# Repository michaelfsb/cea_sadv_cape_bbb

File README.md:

# cea_sadv_cape_bbb
Projeto no KiCad de um módulo para aquisição dados em voo realizado no projeto de Iniciação Cientifica intitulado "Modernização do Sistema de Aquisição de Dados de Voo do CEA".

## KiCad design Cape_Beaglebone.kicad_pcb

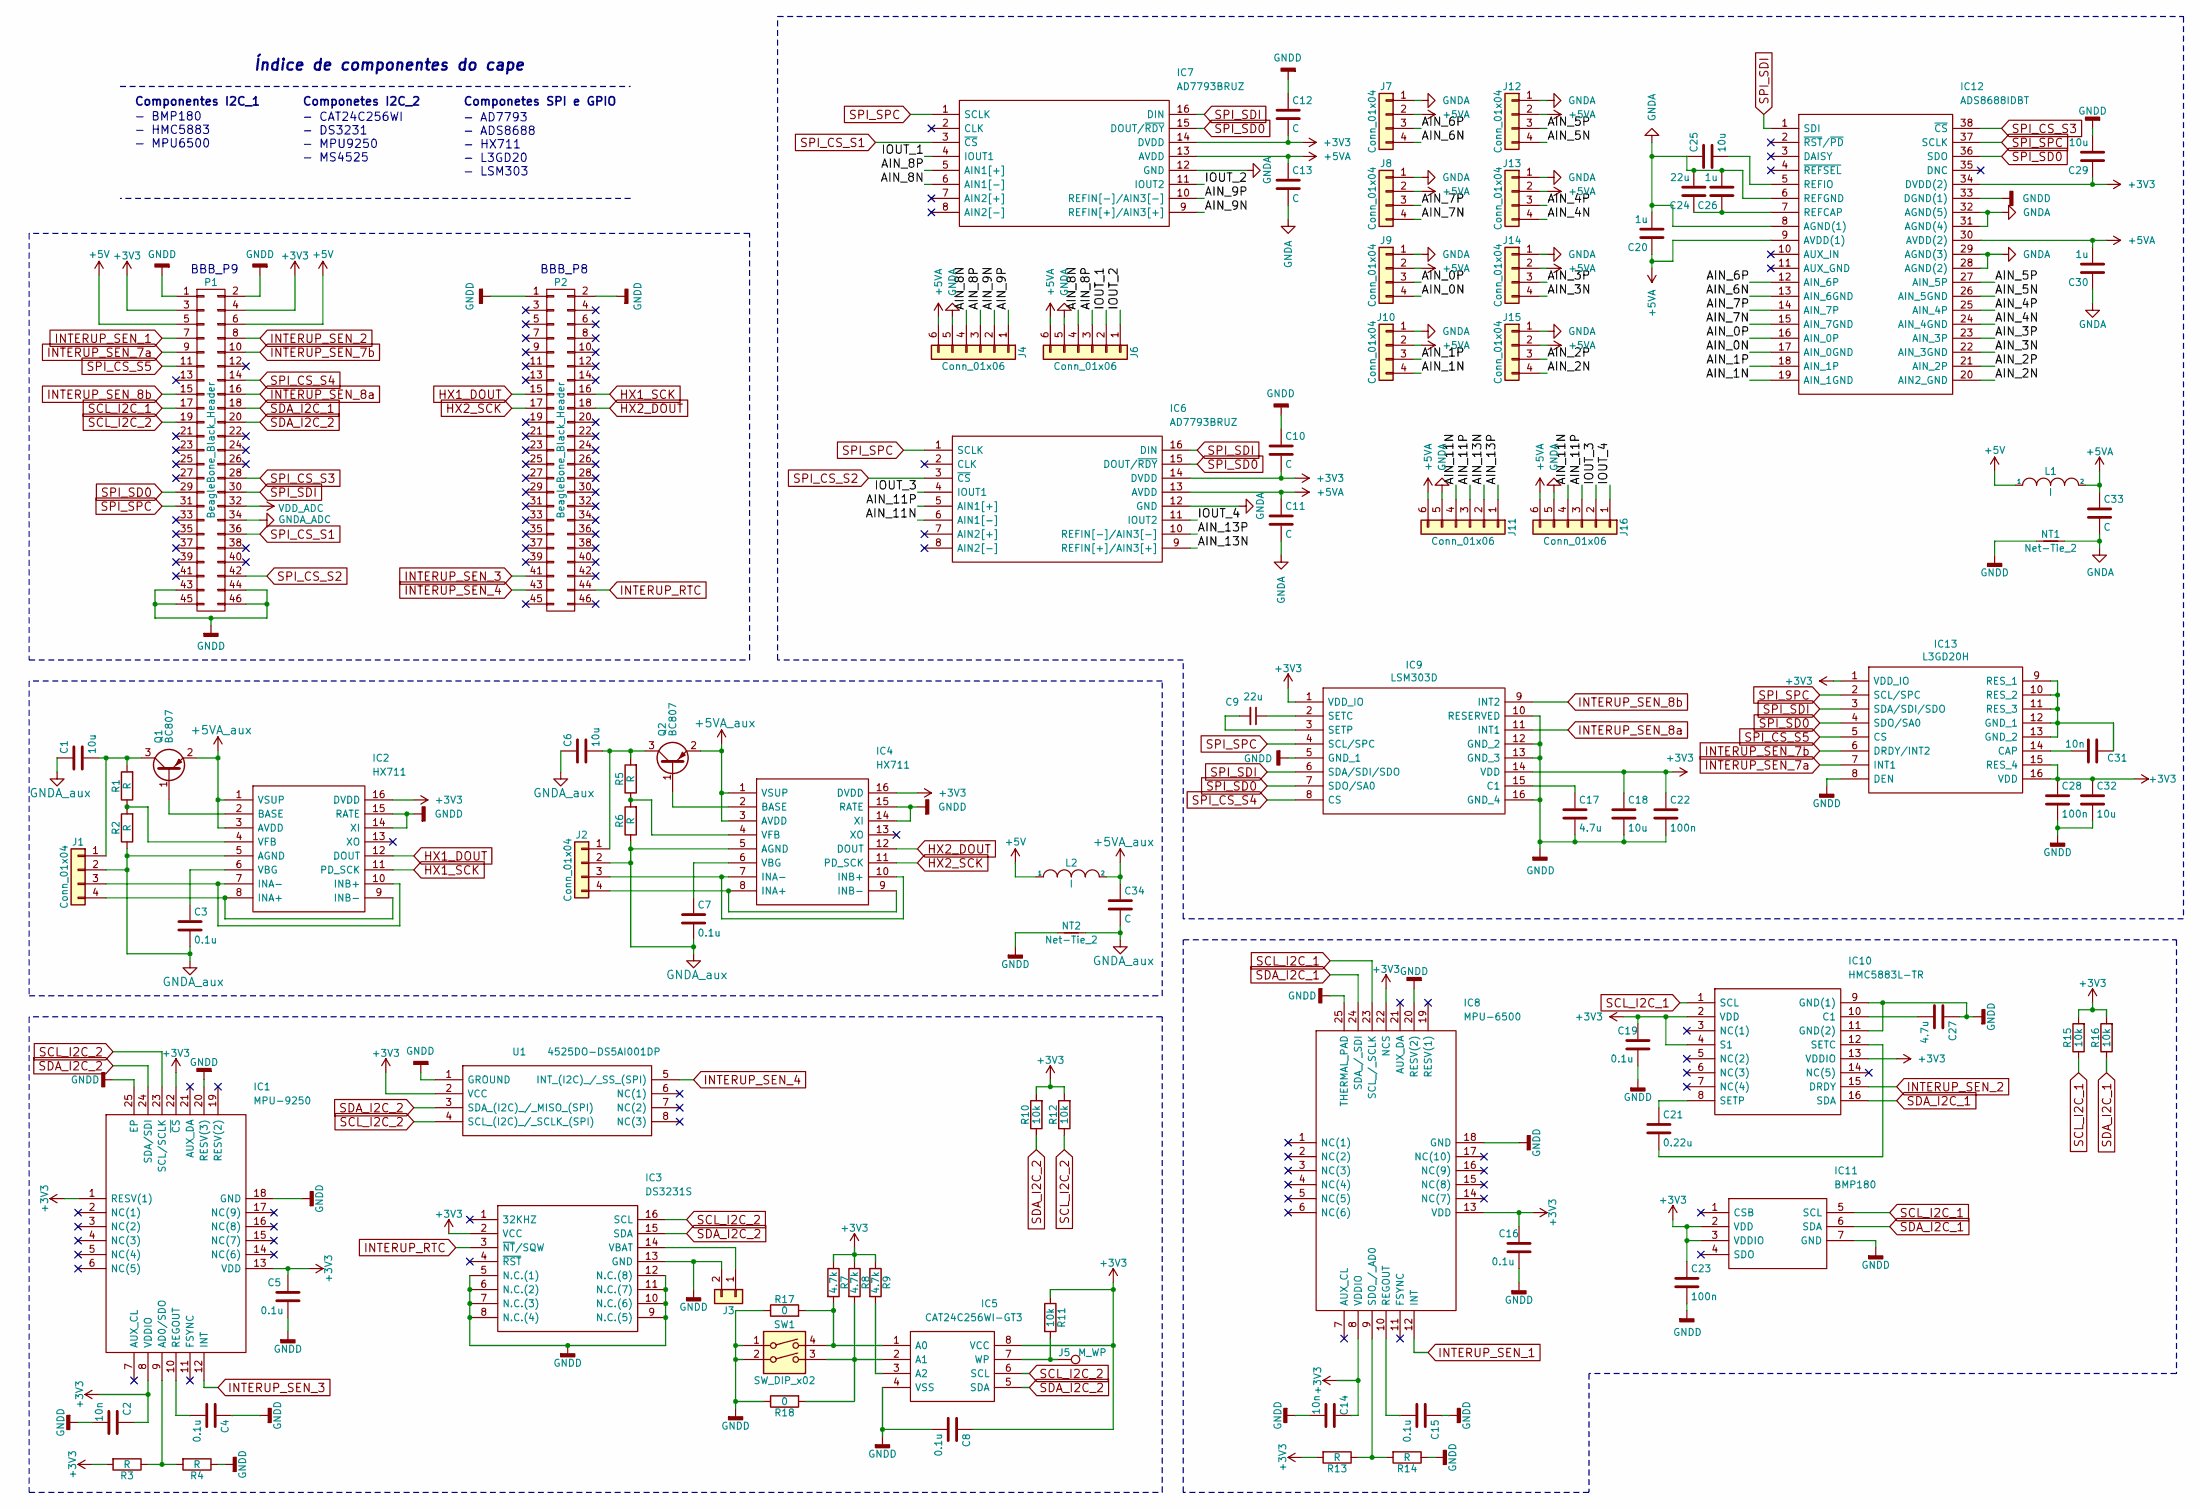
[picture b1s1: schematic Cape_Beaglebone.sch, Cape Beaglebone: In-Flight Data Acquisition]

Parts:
C1, C6, C18, C25, C29, C32: 10u; C_0805
C2, C14, C31: 10n; C_0805
C3, C4, C5, C7, C8, C15, C16, C19: 0.1u; C_0805
C9, C24: 22u; C_0805
C10, C11, C12, C13, C33, C34: C; C_0805
C17, C27: 4.7u; C_0805
C20, C26, C30: 1u; C_0805
C21: 0.22u; C_0805
C22, C23, C28: 100n; C_0805
IC1: MPU-9250; QFN40P300X300X105-25N-D; Manufacturer_Part_Number MPU-9250
IC2, IC4: HX711; SOIC127P600X160-16N; Manufacturer_Part_Number HX711
IC3: DS3231S; SOIC127P1032X265-16N; Manufacturer_Part_Number DS3231S#
IC5: CAT24C256WI-GT3; SOIC127P800X203-8N; Manufacturer_Part_Number CAT24C256WI-GT3
IC6, IC7: AD7793BRUZ; SOP65P640X120-16N; Manufacturer_Part_Number AD7793BRUZ
IC8: MPU-6500; QFN40P300X300X95-25N-D; Manufacturer_Part_Number MPU-6500
IC9: LSM303D; PQFN50P300X300X100-16N; Manufacturer_Part_Number LSM303D
IC10: HMC5883L-TR; 16-PIN-LPCC; Manufacturer_Part_Number HMC5883L-TR
IC11: BMP180; Manufacturer_Part_Number BMP180
IC12: ADS8688IDBT; SOP50P640X120-38N; Manufacturer_Part_Number ADS8688IDBT
IC13: L3GD20H; LGA(3X3X1.0-16L); Manufacturer_Part_Number L3GD20H
J1, J2, J7, J8, J9, J10, J12, J13, J14, J15: Conn_01x04; JST_SH_BM04B-SRSS-TB_04x1.00mm_Straight
J3: Conn_01x02; JST_SH_BM02B-SRSS-TB_02x1.00mm_Straight
J4, J6, J11, J16: Conn_01x06; JST_SH_BM06B-SRSS-TB_06x1.00mm_Straight
J5: M_WP; test_pad
L1, L2: I; R_Axial_DIN0204_L3.6mm_D1.6mm_P7.62mm_Horizontal
NT1, NT2: Net-Tie_2; net_tie2
P1, P2: BeagleBone_Black_Header; Socket_BeagleBone_Black
Q1, Q2: BC807; SOT-23
R1, R2, R3, R4, R5, R6, R13, R14: R; R_0603
R7, R8, R9: 4.7k; R_0603
R10, R11, R12, R15, R16: 10k; R_0603
R17, R18: 0; R_0603
SW1: SW_DIP_x02; SW_DIP_x2_W5.08mm_Slide_Copal_CHS-A
U1: 4525DO-DS5AI001DP; 4525DO-DS...P; Manufacturer_Part_Number 4525DO-DS5AI001DP

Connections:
+3V3: C2.1, C5.1, C8.1, C10.2, C12.2, C14.1, C16.1, C18.1, C19.1, C22.1, C23.1, C28.1, C29.1, C32.1, IC1.1 (RESV(1)), IC1.8 (VDDIO), IC1.13 (VDD), IC1.22 (~CS), IC2.16 (DVDD), IC3.2 (VCC), IC4.16 (DVDD), IC5.8 (VCC), IC6.14 (DVDD), IC7.14 (DVDD), IC8.8 (VDDIO), IC8.13 (VDD), IC8.22 (NCS), IC9.1 (VDD_IO), IC9.14 (VDD), IC10.2 (VDD), IC10.4 (S1), IC10.13 (VDDIO), IC11.2 (VDD), IC11.3 (VDDIO), IC12.34 (DVDD(2)), IC13.1 (VDD_IO), IC13.15 (RES_4), IC13.16 (VDD), P1.3, P1.4, R3.2, R7.1, R8.1, R9.1, R10.2, R11.1, R12.2, R13.2, R15.2, R16.2, U1.2 (VCC); also elsewhere on the board
+5V: L1.1, L2.1, P1.5, P1.6; also elsewhere on the board
+5VA: C11.1, C13.1, C20.1, C30.2, C33.1, IC6.13 (AVDD), IC7.13 (AVDD), IC12.9 (AVDD(1)), IC12.30 (AVDD(2)), J4.6, J6.6, J7.2, J8.2, J9.2, J10.2, J11.6, J12.2, J13.2, J14.2, J15.2, J16.6, L1.2
+5VA_aux: C34.1, IC2.1 (VSUP), IC2.3 (AVDD), IC4.1 (VSUP), IC4.3 (AVDD), L2.2, Q1.2 (E), Q2.2 (E)
/AIN_0N: IC12.17 (AIN_0GND), J9.4
/AIN_0P: IC12.16 (AIN_0P), J9.3
/AIN_1N: IC12.19 (AIN_1GND), J10.4
/AIN_1P: IC12.18 (AIN_1P), J10.3
/AIN_2N: IC12.20 (AIN2_GND), J15.4
/AIN_2P: IC12.21 (AIN_2P), J15.3
/AIN_3N: IC12.22 (AIN_3GND), J14.4
/AIN_3P: IC12.23 (AIN_3P), J14.3
/AIN_4N: IC12.24 (AIN_4GND), J13.4
/AIN_4P: IC12.25 (AIN_4P), J13.3
/AIN_5N: IC12.26 (AIN_5GND), J12.4
/AIN_5P: IC12.27 (AIN_5P), J12.3
/AIN_6N: IC12.13 (AIN_6GND), J7.4
/AIN_6P: IC12.12 (AIN_6P), J7.3
/AIN_7N: IC12.15 (AIN_7GND), J8.4
/AIN_7P: IC12.14 (AIN_7P), J8.3
/AIN_8N: IC7.6 (AIN1[-]), J4.4, J6.4
/AIN_8P: IC7.5 (AIN1[+]), J4.3, J6.3
/AIN_9N: IC7.9 (REFIN[+]/AIN3[+]), J4.2
/AIN_9P: IC7.10 (REFIN[-]/AIN3[-]), J4.1
/AIN_11N: IC6.6 (AIN1[-]), J11.4, J16.4
/AIN_11P: IC6.5 (AIN1[+]), J11.3, J16.3
/AIN_13N: IC6.9 (REFIN[+]/AIN3[+]), J11.2
/AIN_13P: IC6.10 (REFIN[-]/AIN3[-]), J11.1
/IOUT_1: IC7.4 (IOUT1), J6.2
/IOUT_2: IC7.11 (IOUT2), J6.1
/IOUT_3: IC6.4 (IOUT1), J16.2
/IOUT_4: IC6.11 (IOUT2), J16.1
GNDA: C11.2, C13.2, C20.2, C24.2, C25.1, C26.2, C30.1, C33.2, IC6.12 (GND), IC7.12 (GND), IC12.6 (REFGND), IC12.8 (AGND(1)), IC12.28 (AGND(2)), IC12.29 (AGND(3)), IC12.31 (AGND(4)), IC12.32 (AGND(5)), J4.5, J6.5, J7.1, J8.1, J9.1, J10.1, J11.5, J12.1, J13.1, J14.1, J15.1, J16.5, NT1.2
GNDA_aux: C1.1, C3.2, C6.1, C7.2, C34.2, IC2.5 (AGND), IC4.5 (AGND), J1.2, J2.2, NT2.2, R2.1, R6.1
GNDD: C2.2, C4.1, C5.2, C8.2, C10.1, C12.1, C14.2, C15.1, C16.2, C17.2, C18.2, C19.2, C22.2, C23.2, C27.1, C28.2, C29.2, C32.2, IC1.18 (GND), IC1.20 (RESV(3)), IC1.25 (EP), IC2.14 (XI), IC2.15 (RATE), IC3.5 (N.C.(1)), IC3.6 (N.C.(2)), IC3.7 (N.C.(3)), IC3.8 (N.C.(4)), IC3.9 (N.C.(5)), IC3.10 (N.C.(6)), IC3.11 (N.C.(7)), IC3.12 (N.C.(8)), IC3.13 (GND), IC4.14 (XI), IC4.15 (RATE), IC5.4 (VSS), IC8.18 (GND), IC8.20 (RESV(2)), IC8.25 (THERMAL_PAD), IC9.5 (GND_1), IC9.10 (RESERVED), IC9.12 (GND_2), IC9.13 (GND_3), IC9.16 (GND_4), IC10.9 (GND(1)), IC10.11 (GND(2)), IC11.7 (GND), IC12.33 (DGND(1)), IC13.8 (DEN), J3.2, NT1.1, NT2.1, P1.1, P1.2, P1.43, P1.44, P1.45, P1.46, P2.1, P2.2, R4.1, R14.1, R17.1, R18.1, SW1.1, SW1.2, U1.1 (GROUND); also elsewhere on the board
HX1_DOUT: IC2.12 (DOUT), P2.15; also elsewhere on the board
HX1_SCK: IC2.11 (PD_SCK), P2.16; also elsewhere on the board
HX2_DOUT: IC4.12 (DOUT), P2.18; also elsewhere on the board
HX2_SCK: IC4.11 (PD_SCK), P2.17; also elsewhere on the board
INTERUP_RTC: IC3.3 (~NT~/SQW), P2.44; also elsewhere on the board
INTERUP_SEN_1: IC8.12 (INT), P1.7; also elsewhere on the board
INTERUP_SEN_2: IC10.15 (DRDY), P1.8; also elsewhere on the board
INTERUP_SEN_3: IC1.12 (INT), P2.41; also elsewhere on the board
INTERUP_SEN_4: P2.43, U1.5 (INT_(I2C)_/_SS_(SPI)); also elsewhere on the board
INTERUP_SEN_7a: IC13.7 (INT1), P1.9; also elsewhere on the board
INTERUP_SEN_7b: IC13.6 (DRDY/INT2), P1.10; also elsewhere on the board
INTERUP_SEN_8a: IC9.11 (INT1), P1.16; also elsewhere on the board
INTERUP_SEN_8b: IC9.9 (INT2), P1.15; also elsewhere on the board
unnamed: C1.2, J1.1, Q1.3 (C), R1.2
unnamed: C3.1, IC2.6 (VBG)
unnamed: C4.2, IC1.10 (REGOUT)
unnamed: C6.2, J2.1, Q2.3 (C), R5.2
unnamed: C7.1, IC4.6 (VBG)
unnamed: C9.1, IC9.2 (SETC)
unnamed: C9.2, IC9.3 (SETP)
unnamed: C15.2, IC8.10 (REGOUT)
unnamed: C17.1, IC9.15 (C1)
unnamed: C21.1, IC10.8 (SETP)
unnamed: C21.2, IC10.12 (SETC)
unnamed: C24.1, C26.1, IC12.7 (REFCAP)
unnamed: C25.2, IC12.5 (REFIO)
unnamed: C27.2, IC10.10 (C1)
unnamed: C31.1, IC13.9 (RES_1), IC13.10 (RES_2), IC13.11 (RES_3), IC13.12 (GND_1), IC13.13 (GND_2)
unnamed: C31.2, IC13.14 (CAP)
unnamed: IC1.9 (AD0/SDO), R3.1, R4.2
unnamed: IC2.2 (BASE), Q1.1 (B)
unnamed: IC2.4 (VFB), R1.1, R2.2
unnamed: IC2.8 (INA+), IC2.9 (INB-), J1.4
unnamed: IC2.7 (INA-), IC2.10 (INB+), J1.3
unnamed: IC3.14 (VBAT), J3.1
unnamed: IC4.2 (BASE), Q2.1 (B)
unnamed: IC4.4 (VFB), R5.1, R6.2
unnamed: IC4.8 (INA+), IC4.9 (INB-), J2.4
unnamed: IC4.7 (INA-), IC4.10 (INB+), J2.3
unnamed: IC5.1 (A0), R7.2, R17.2, SW1.4
unnamed: IC5.2 (A1), R8.2, R18.2, SW1.3
unnamed: IC5.3 (A2), R9.2
unnamed: IC5.7 (WP), J5.1, R11.2
unnamed: IC8.9 (SDO_/_AD0), R13.1, R14.2
SCL_I2C_1: IC8.23 (SCL_/_SCLK), IC10.1 (SCL), IC11.5 (SCL), P1.17, R15.1; also elsewhere on the board
SCL_I2C_2: IC1.23 (SCL/SCLK), IC3.16 (SCL), IC5.6 (SCL), P1.19, R12.1, U1.4 (SCL_(I2C)_/_SCLK_(SPI)); also elsewhere on the board
SDA_I2C_1: IC8.24 (SDA_/_SDI), IC10.16 (SDA), IC11.6 (SDA), P1.18, R16.1; also elsewhere on the board
SDA_I2C_2: IC1.24 (SDA/SDI), IC3.15 (SDA), IC5.5 (SDA), P1.20, R10.1, U1.3 (SDA_(I2C)_/_MISO_(SPI)); also elsewhere on the board
SPI_CS_S1: IC7.3 (~CS), P1.36; also elsewhere on the board
SPI_CS_S2: IC6.3 (~CS), P1.42; also elsewhere on the board
SPI_CS_S3: IC12.38 (~CS), P1.28; also elsewhere on the board
SPI_CS_S4: IC9.8 (CS), P1.14; also elsewhere on the board
SPI_CS_S5: IC13.5 (CS), P1.11; also elsewhere on the board
SPI_SD0: IC6.15 (DOUT/~RDY), IC7.15 (DOUT/~RDY), IC9.7 (SDO/SA0), IC12.36 (SDO), IC13.4 (SDO/SA0), P1.29; also elsewhere on the board
SPI_SDI: IC6.16 (DIN), IC7.16 (DIN), IC9.6 (SDA/SDI/SDO), IC12.1 (SDI), IC13.3 (SDA/SDI/SDO), P1.30; also elsewhere on the board
SPI_SPC: IC6.1 (SCLK), IC7.1 (SCLK), IC9.4 (SCL/SPC), IC12.37 (SCLK), IC13.2 (SCL/SPC), P1.31; also elsewhere on the board

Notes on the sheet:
- BMP180 - HMC5883 - MPU6500
Componentes I2C_1
Componetes I2C_2
- CAT24C256WI - DS3231 - MPU9250 - MS4525
Componetes SPI e GPIO
- AD7793 - ADS8688 - HX711 - L3GD20 - LSM303
Índice de componentes do cape
BBB_P8
BBB_P9

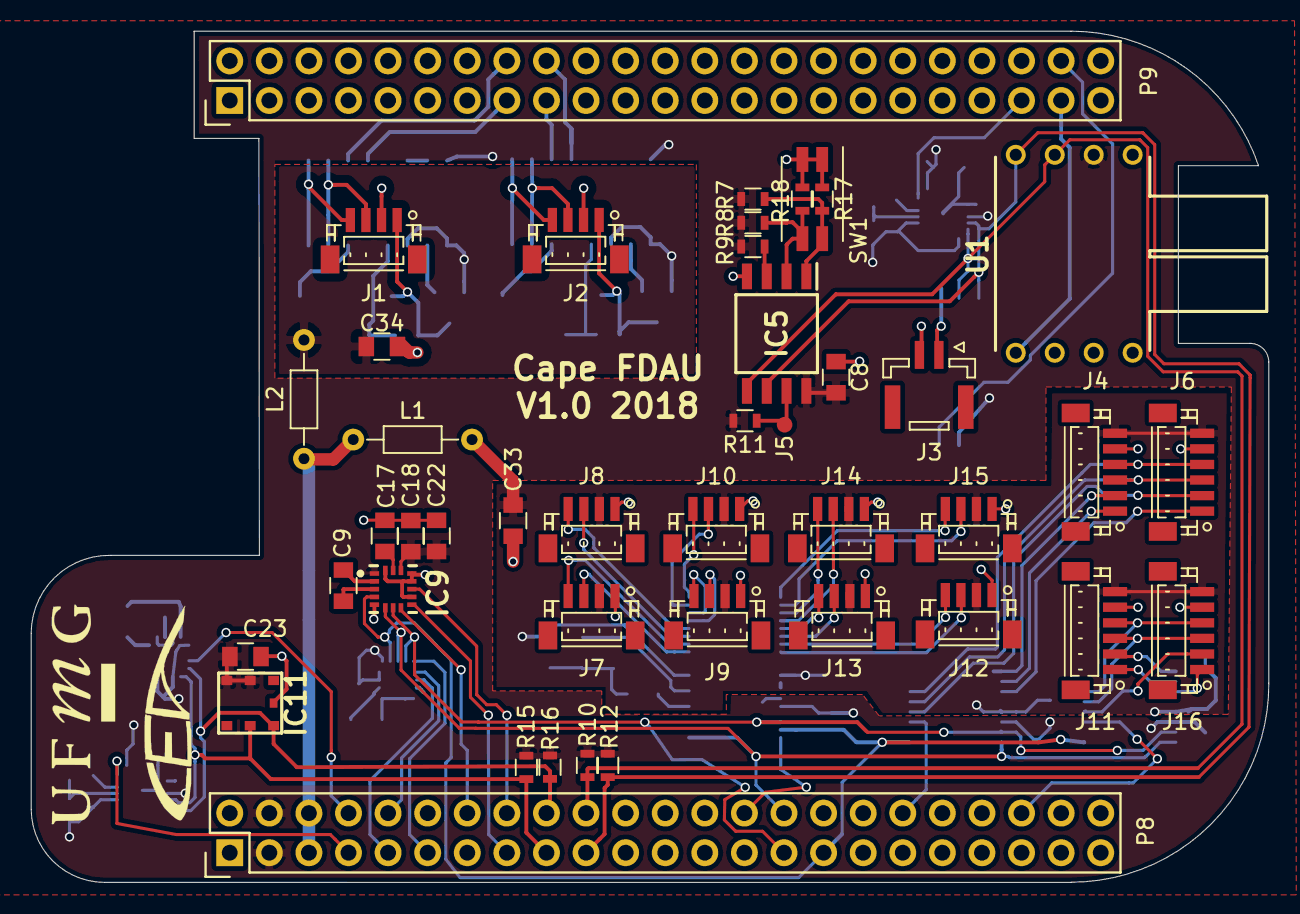
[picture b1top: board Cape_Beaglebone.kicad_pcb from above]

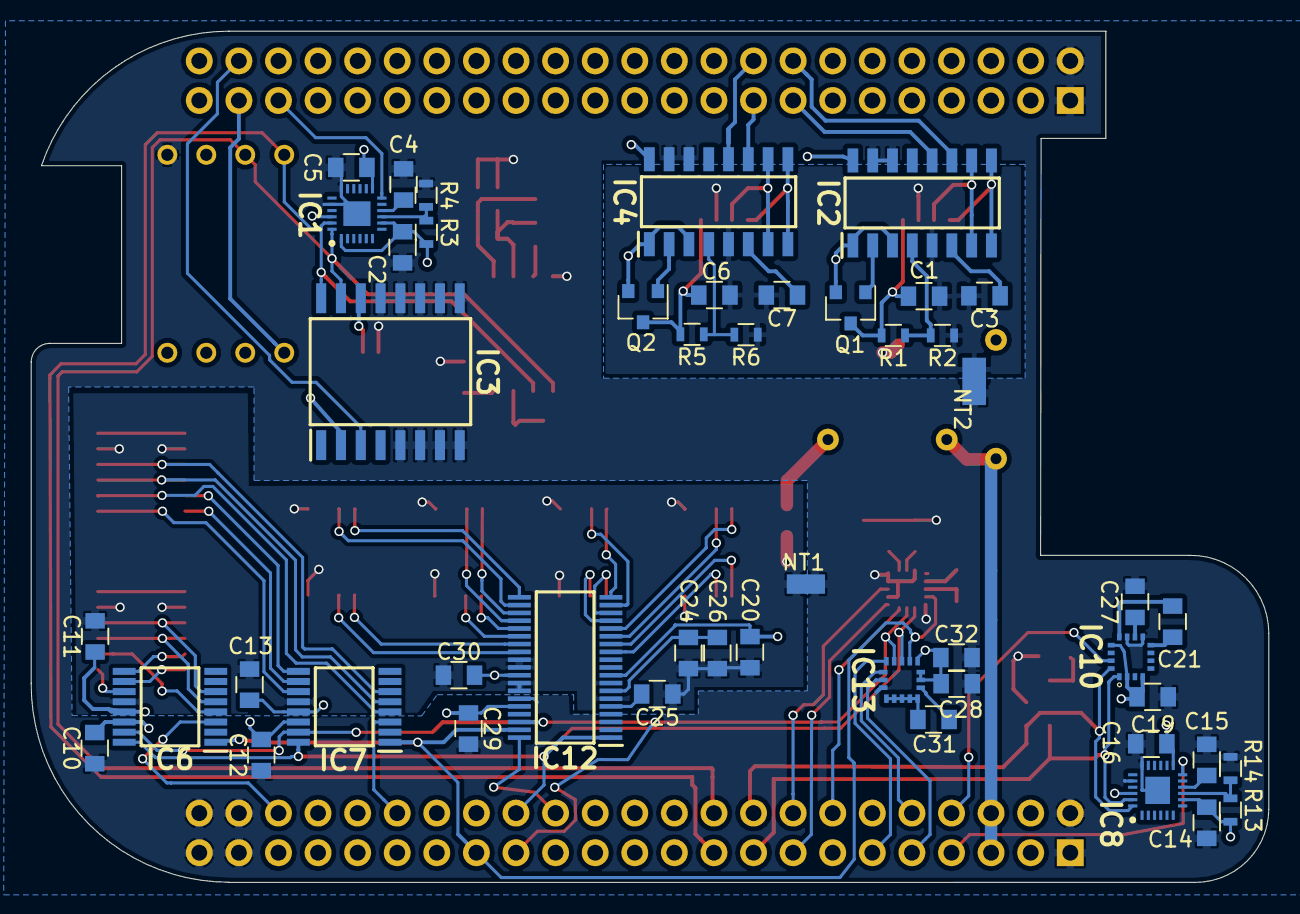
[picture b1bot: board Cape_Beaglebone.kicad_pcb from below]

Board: 2 copper layers, 79.4 x 54.6 mm, 91 parts (48 on the bottom side), 91 nets.

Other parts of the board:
P8, P9: BeagleBone_Black_Header; Socket_BeagleBone_Black

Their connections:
+3V3: P8.3, P8.4; also elsewhere on the board
+5V: P8.5, P8.6; also elsewhere on the board
GNDD: P8.1, P8.2, P8.43, P8.44, P8.45, P8.46, P9.1, P9.2; also elsewhere on the board
HX1_DOUT: P9.15; also elsewhere on the board
HX1_SCK: P9.16; also elsewhere on the board
HX2_DOUT: P9.18; also elsewhere on the board
HX2_SCK: P9.17; also elsewhere on the board
INTERUP_RTC: P9.44; also elsewhere on the board
INTERUP_SEN_1: P8.7; also elsewhere on the board
INTERUP_SEN_2: P8.8; also elsewhere on the board
INTERUP_SEN_3: P9.41; also elsewhere on the board
INTERUP_SEN_4: P9.43; also elsewhere on the board
INTERUP_SEN_7a: P8.9; also elsewhere on the board
INTERUP_SEN_7b: P8.10; also elsewhere on the board
INTERUP_SEN_8a: P8.16; also elsewhere on the board
INTERUP_SEN_8b: P8.15; also elsewhere on the board
SCL_I2C_1: P8.17; also elsewhere on the board
SCL_I2C_2: P8.19; also elsewhere on the board
SDA_I2C_1: P8.18; also elsewhere on the board
SDA_I2C_2: P8.20; also elsewhere on the board
SPI_CS_S1: P8.36; also elsewhere on the board
SPI_CS_S2: P8.42; also elsewhere on the board
SPI_CS_S3: P8.28; also elsewhere on the board
SPI_CS_S4: P8.14; also elsewhere on the board
SPI_CS_S5: P8.11; also elsewhere on the board
SPI_SD0: P8.29; also elsewhere on the board
SPI_SDI: P8.30; also elsewhere on the board
SPI_SPC: P8.31; also elsewhere on the board

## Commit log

2018-07-16 15_07_18
2018-07-29 mfsb_29_07_18
    Primeira tentativa do layout
2018-07-31 Revisões no esquemático do RTC.
2018-07-31 Revisões no esquemático do HX711.
2018-07-31 Revisões no esquemático do AD7793.
2018-07-31 Revisões no esquemático do ADS8688.
2018-08-18 Layout com SJT GH
    Layout quase finalizado usando os conectores SJT GH de 1,25 mm
2018-09-16 Final V1.0
    Primeria versão final sem revisão
2018-09-28 Corte para mangeira
    Alteração para facilitar a colocação de magueira no sensor de pressão
2018-10-21 GNDA
    Correções no ground
2018-11-05 Conector bateiira RTC
    Troca do conector da bateria do RTC de JSH SH para o JST GH. Pois não tinha o SH disponivel para comprar.
2018-11-05 Arquivos Gerber
    Arquivos Gerber
2019-04-26 Atualizando para Kicad 5.1.0
2019-04-27 Corrigindo referências a bibliotecas de símbolos.
2019-04-27 Corrigi erro alias inexistente para VDD_ADC.
